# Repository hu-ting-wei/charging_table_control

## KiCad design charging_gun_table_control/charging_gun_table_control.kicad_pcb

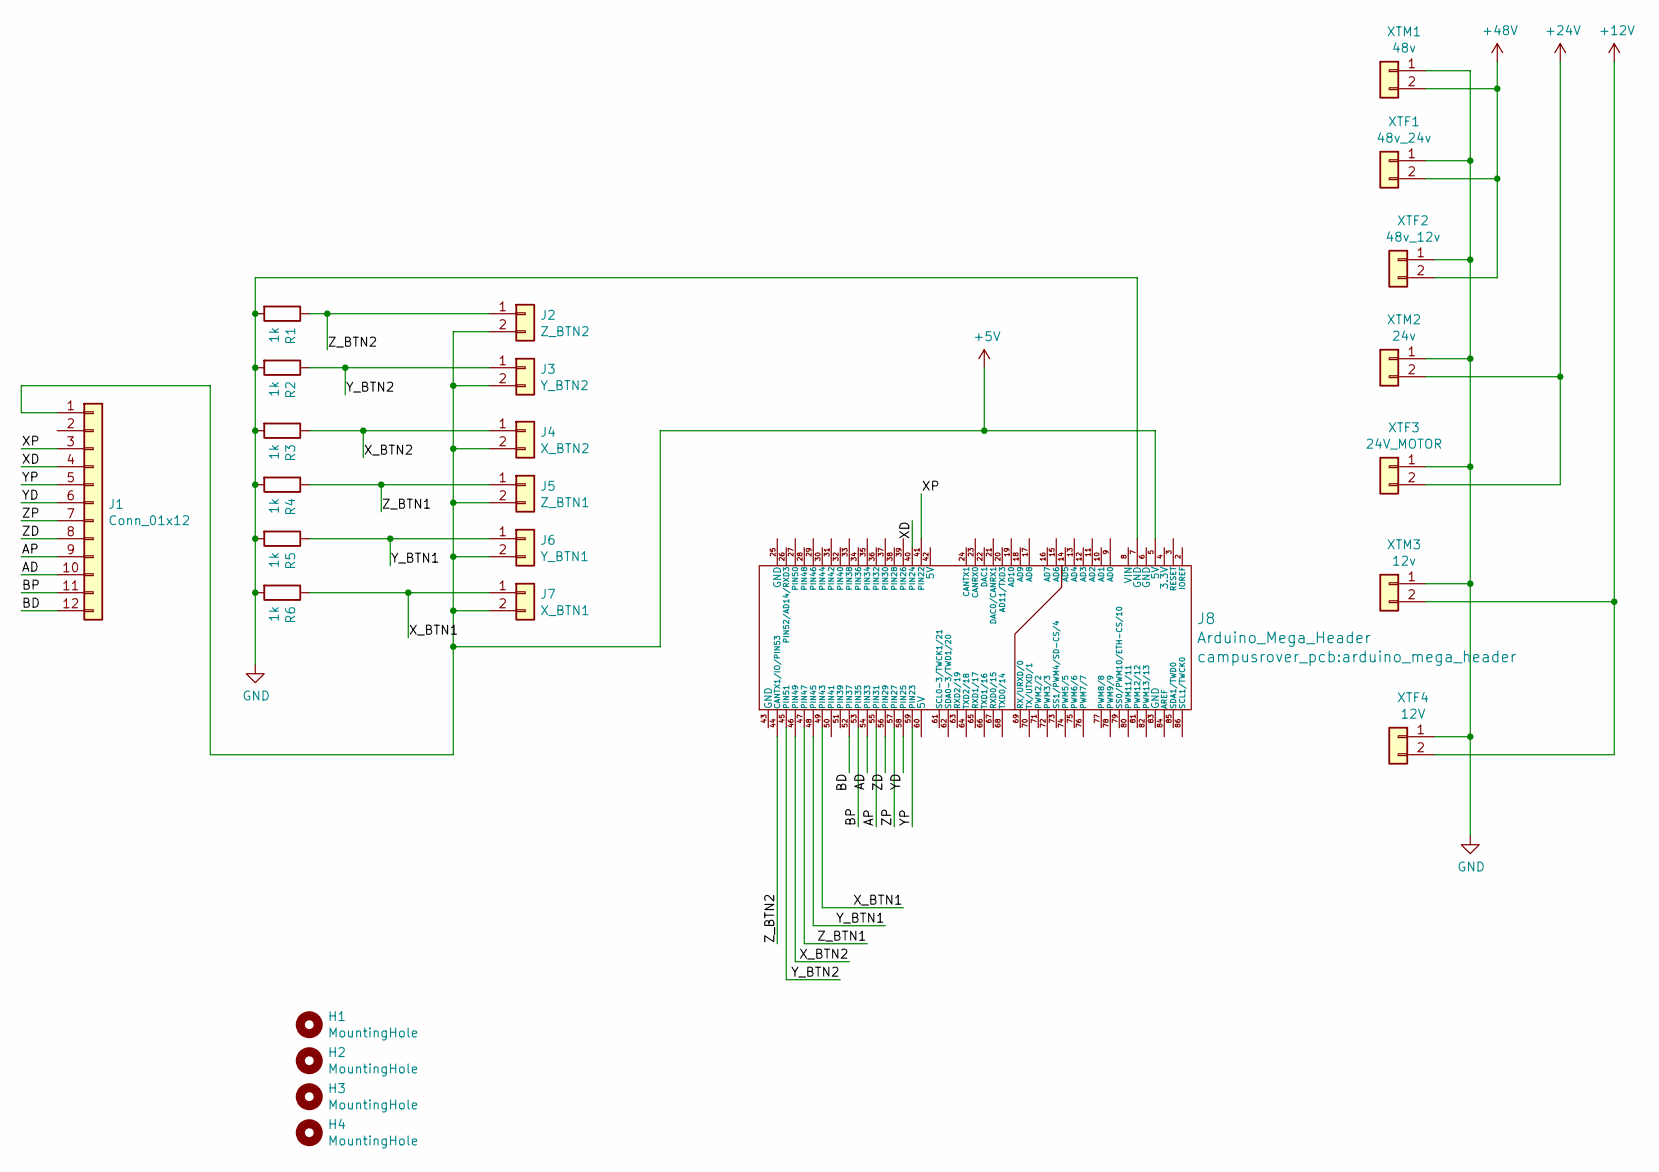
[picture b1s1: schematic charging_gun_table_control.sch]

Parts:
H1, H2, H3, H4: MountingHole; MountingHole_3.2mm_M3
J1: Conn_01x12; PhoenixContact_GMSTBA_2,5_12-G-7,62_1x12_P7.62mm_Horizontal
J2: Z_BTN2; Molex_KK-254_AE-6410-02A_1x02_P2.54mm_Vertical
J3: Y_BTN2; Molex_KK-254_AE-6410-02A_1x02_P2.54mm_Vertical
J4: X_BTN2; Molex_KK-254_AE-6410-02A_1x02_P2.54mm_Vertical
J5: Z_BTN1; Molex_KK-254_AE-6410-02A_1x02_P2.54mm_Vertical
J6: Y_BTN1; Molex_KK-254_AE-6410-02A_1x02_P2.54mm_Vertical
J7: X_BTN1; Molex_KK-254_AE-6410-02A_1x02_P2.54mm_Vertical
J8: Arduino_Mega_Header; arduino_mega_header
R1, R2, R3, R4, R5, R6: 1k; R_Axial_DIN0204_L3.6mm_D1.6mm_P5.08mm_Horizontal
XTF1: 48v_24v; AMASS_XT60-F_1x02_P7.20mm_Vertical
XTF2: 48v_12v; AMASS_XT60-F_1x02_P7.20mm_Vertical
XTF3: 24V_MOTOR; AMASS_XT60-F_1x02_P7.20mm_Vertical
XTF4: 12V; AMASS_XT60-F_1x02_P7.20mm_Vertical
XTM1: 48v; AMASS_XT60-M_1x02_P7.20mm_Vertical
XTM2: 24v; AMASS_XT60-M_1x02_P7.20mm_Vertical
XTM3: 12v; AMASS_XT60-M_1x02_P7.20mm_Vertical

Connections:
+5V: J1.1, J2.2, J3.2, J4.2, J5.2, J6.2, J7.2, J8.5 (5V)
+12V: XTF4.2, XTM3.2
+24V: XTF3.2, XTM2.2
+48V: XTF1.2, XTF2.2, XTM1.2
/AD: J1.10, J8.54 (PIN33)
/AP: J1.9, J8.55 (PIN31)
/BD: J1.12, J8.52 (PIN37)
/BP: J1.11, J8.53 (PIN35)
/XD: J1.4, J8.40 (PIN24)
/XP: J1.3, J8.41 (PIN22)
/X_BTN1: J7.1, J8.49 (PIN43), R6.1
/X_BTN2: J4.1, J8.46 (PIN49), R3.1
/YD: J1.6, J8.58 (PIN25)
/YP: J1.5, J8.59 (PIN23)
/Y_BTN1: J6.1, J8.48 (PIN45), R5.1
/Y_BTN2: J3.1, J8.45 (PIN51), R2.1
/ZD: J1.8, J8.56 (PIN29)
/ZP: J1.7, J8.57 (PIN27)
/Z_BTN1: J5.1, J8.47 (PIN47), R4.1
/Z_BTN2: J2.1, J8.44 (CANTX1/IO/PIN53), R1.1
GND: J8.7 (GND), R1.2, R2.2, R3.2, R4.2, R5.2, R6.2, XTF1.1, XTF2.1, XTF3.1, XTF4.1, XTM1.1, XTM2.1, XTM3.1

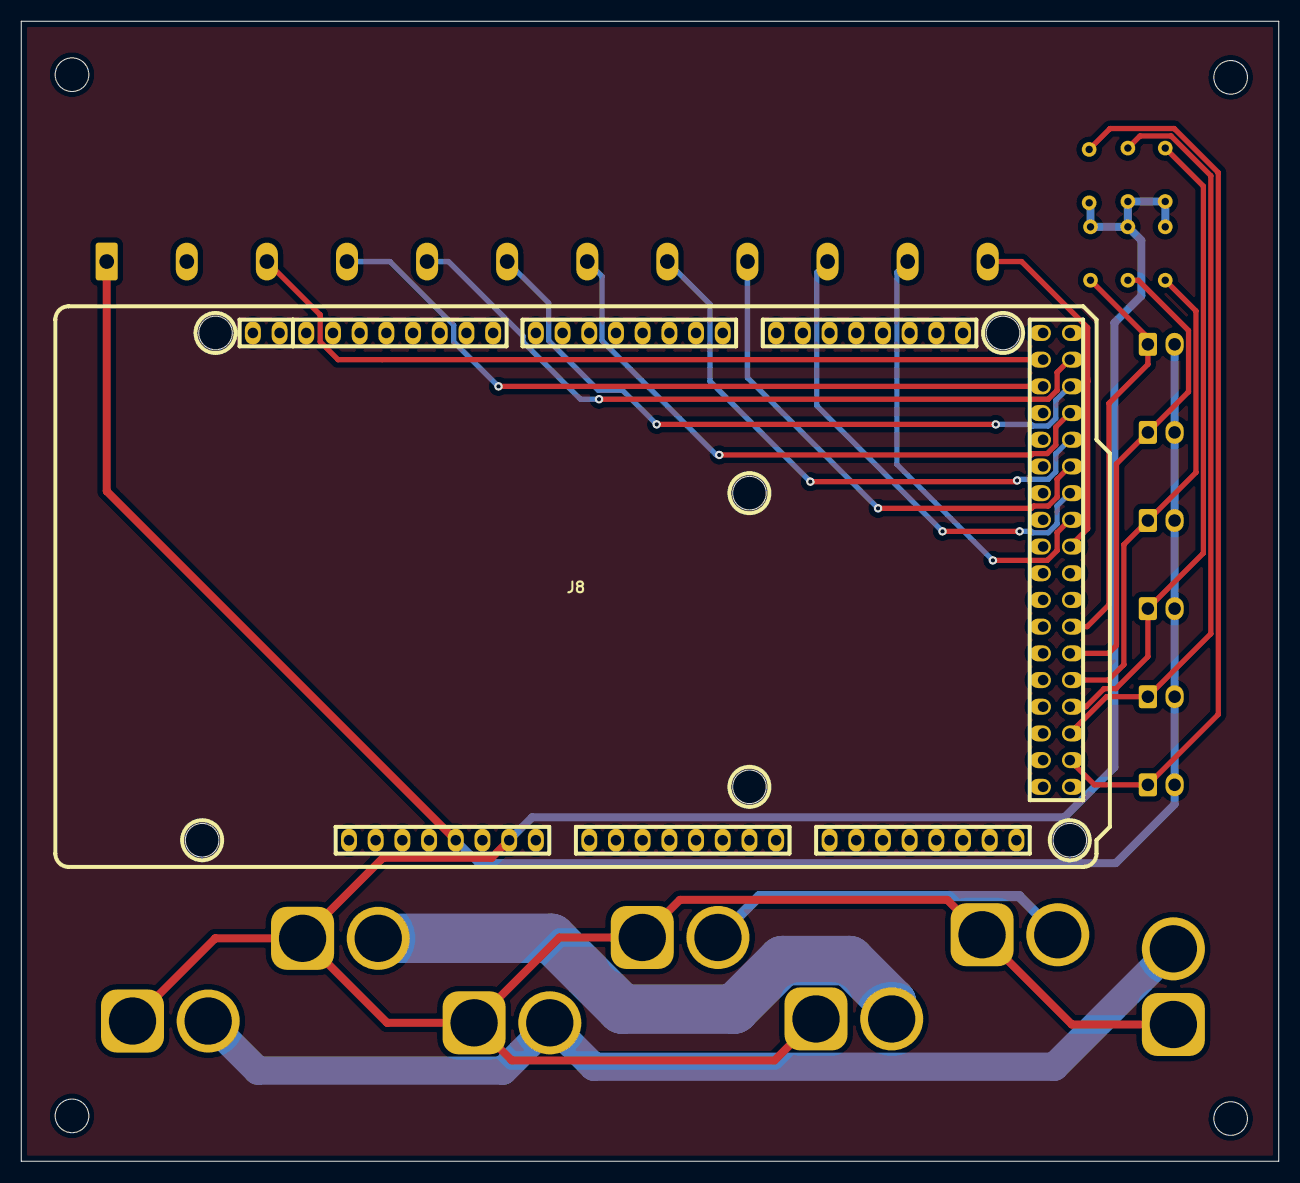
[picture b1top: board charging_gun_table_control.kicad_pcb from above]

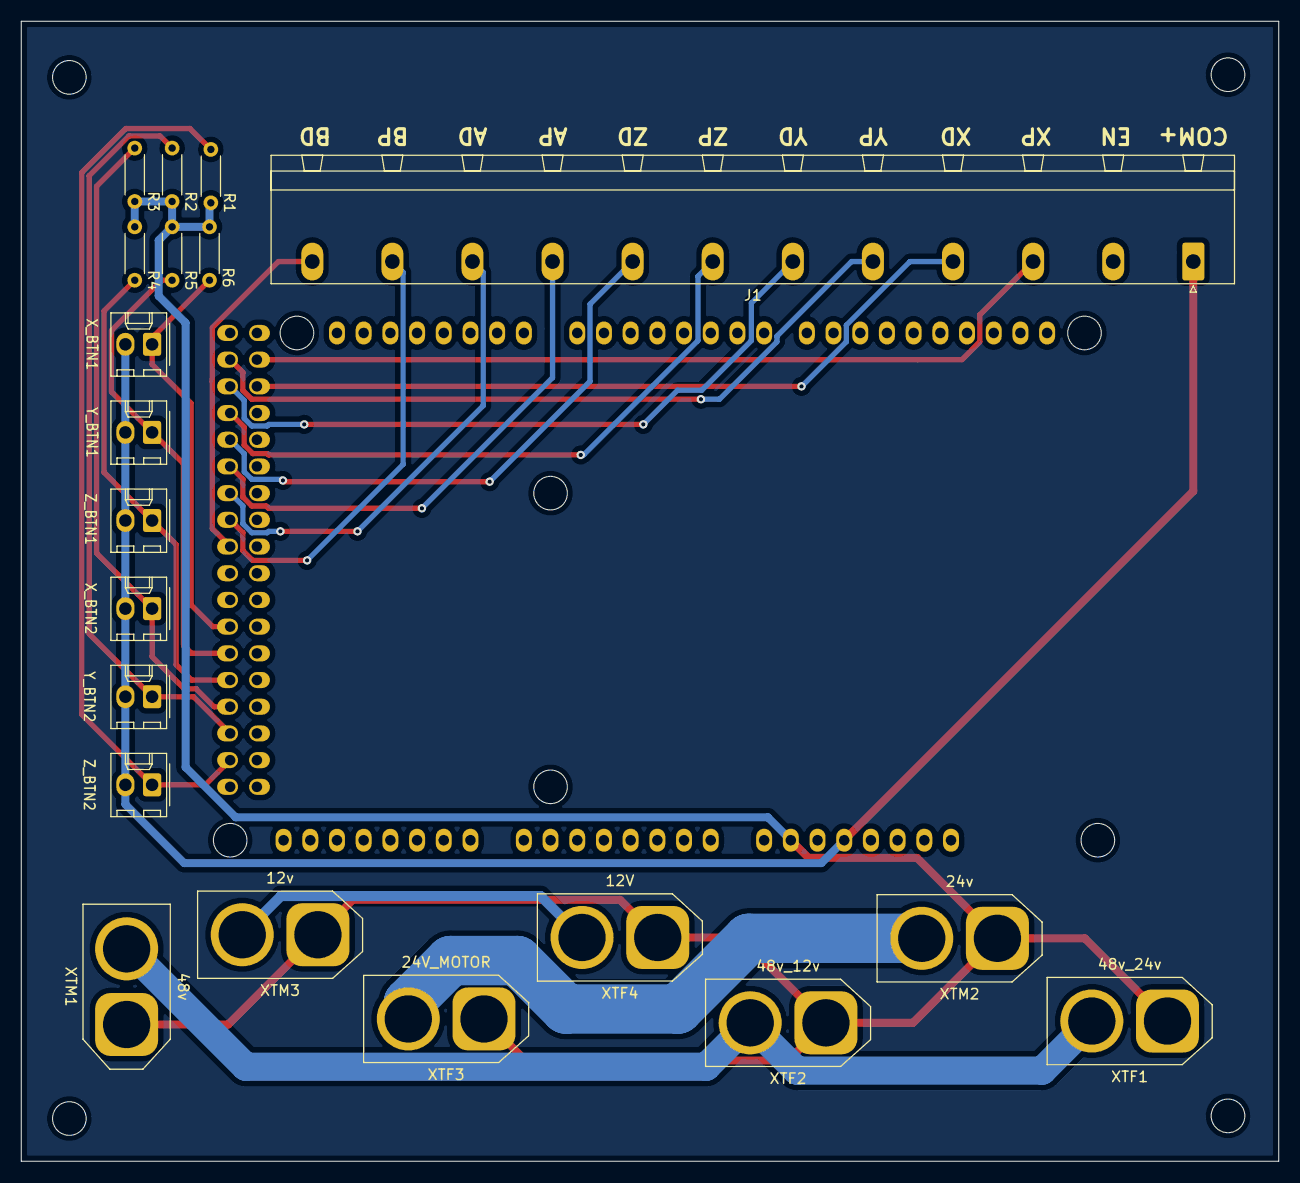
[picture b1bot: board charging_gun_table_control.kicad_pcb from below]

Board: 2 copper layers, 119.6 x 108.5 mm, 25 parts (20 on the bottom side), 21 nets.

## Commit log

2021-05-28 add new folder
